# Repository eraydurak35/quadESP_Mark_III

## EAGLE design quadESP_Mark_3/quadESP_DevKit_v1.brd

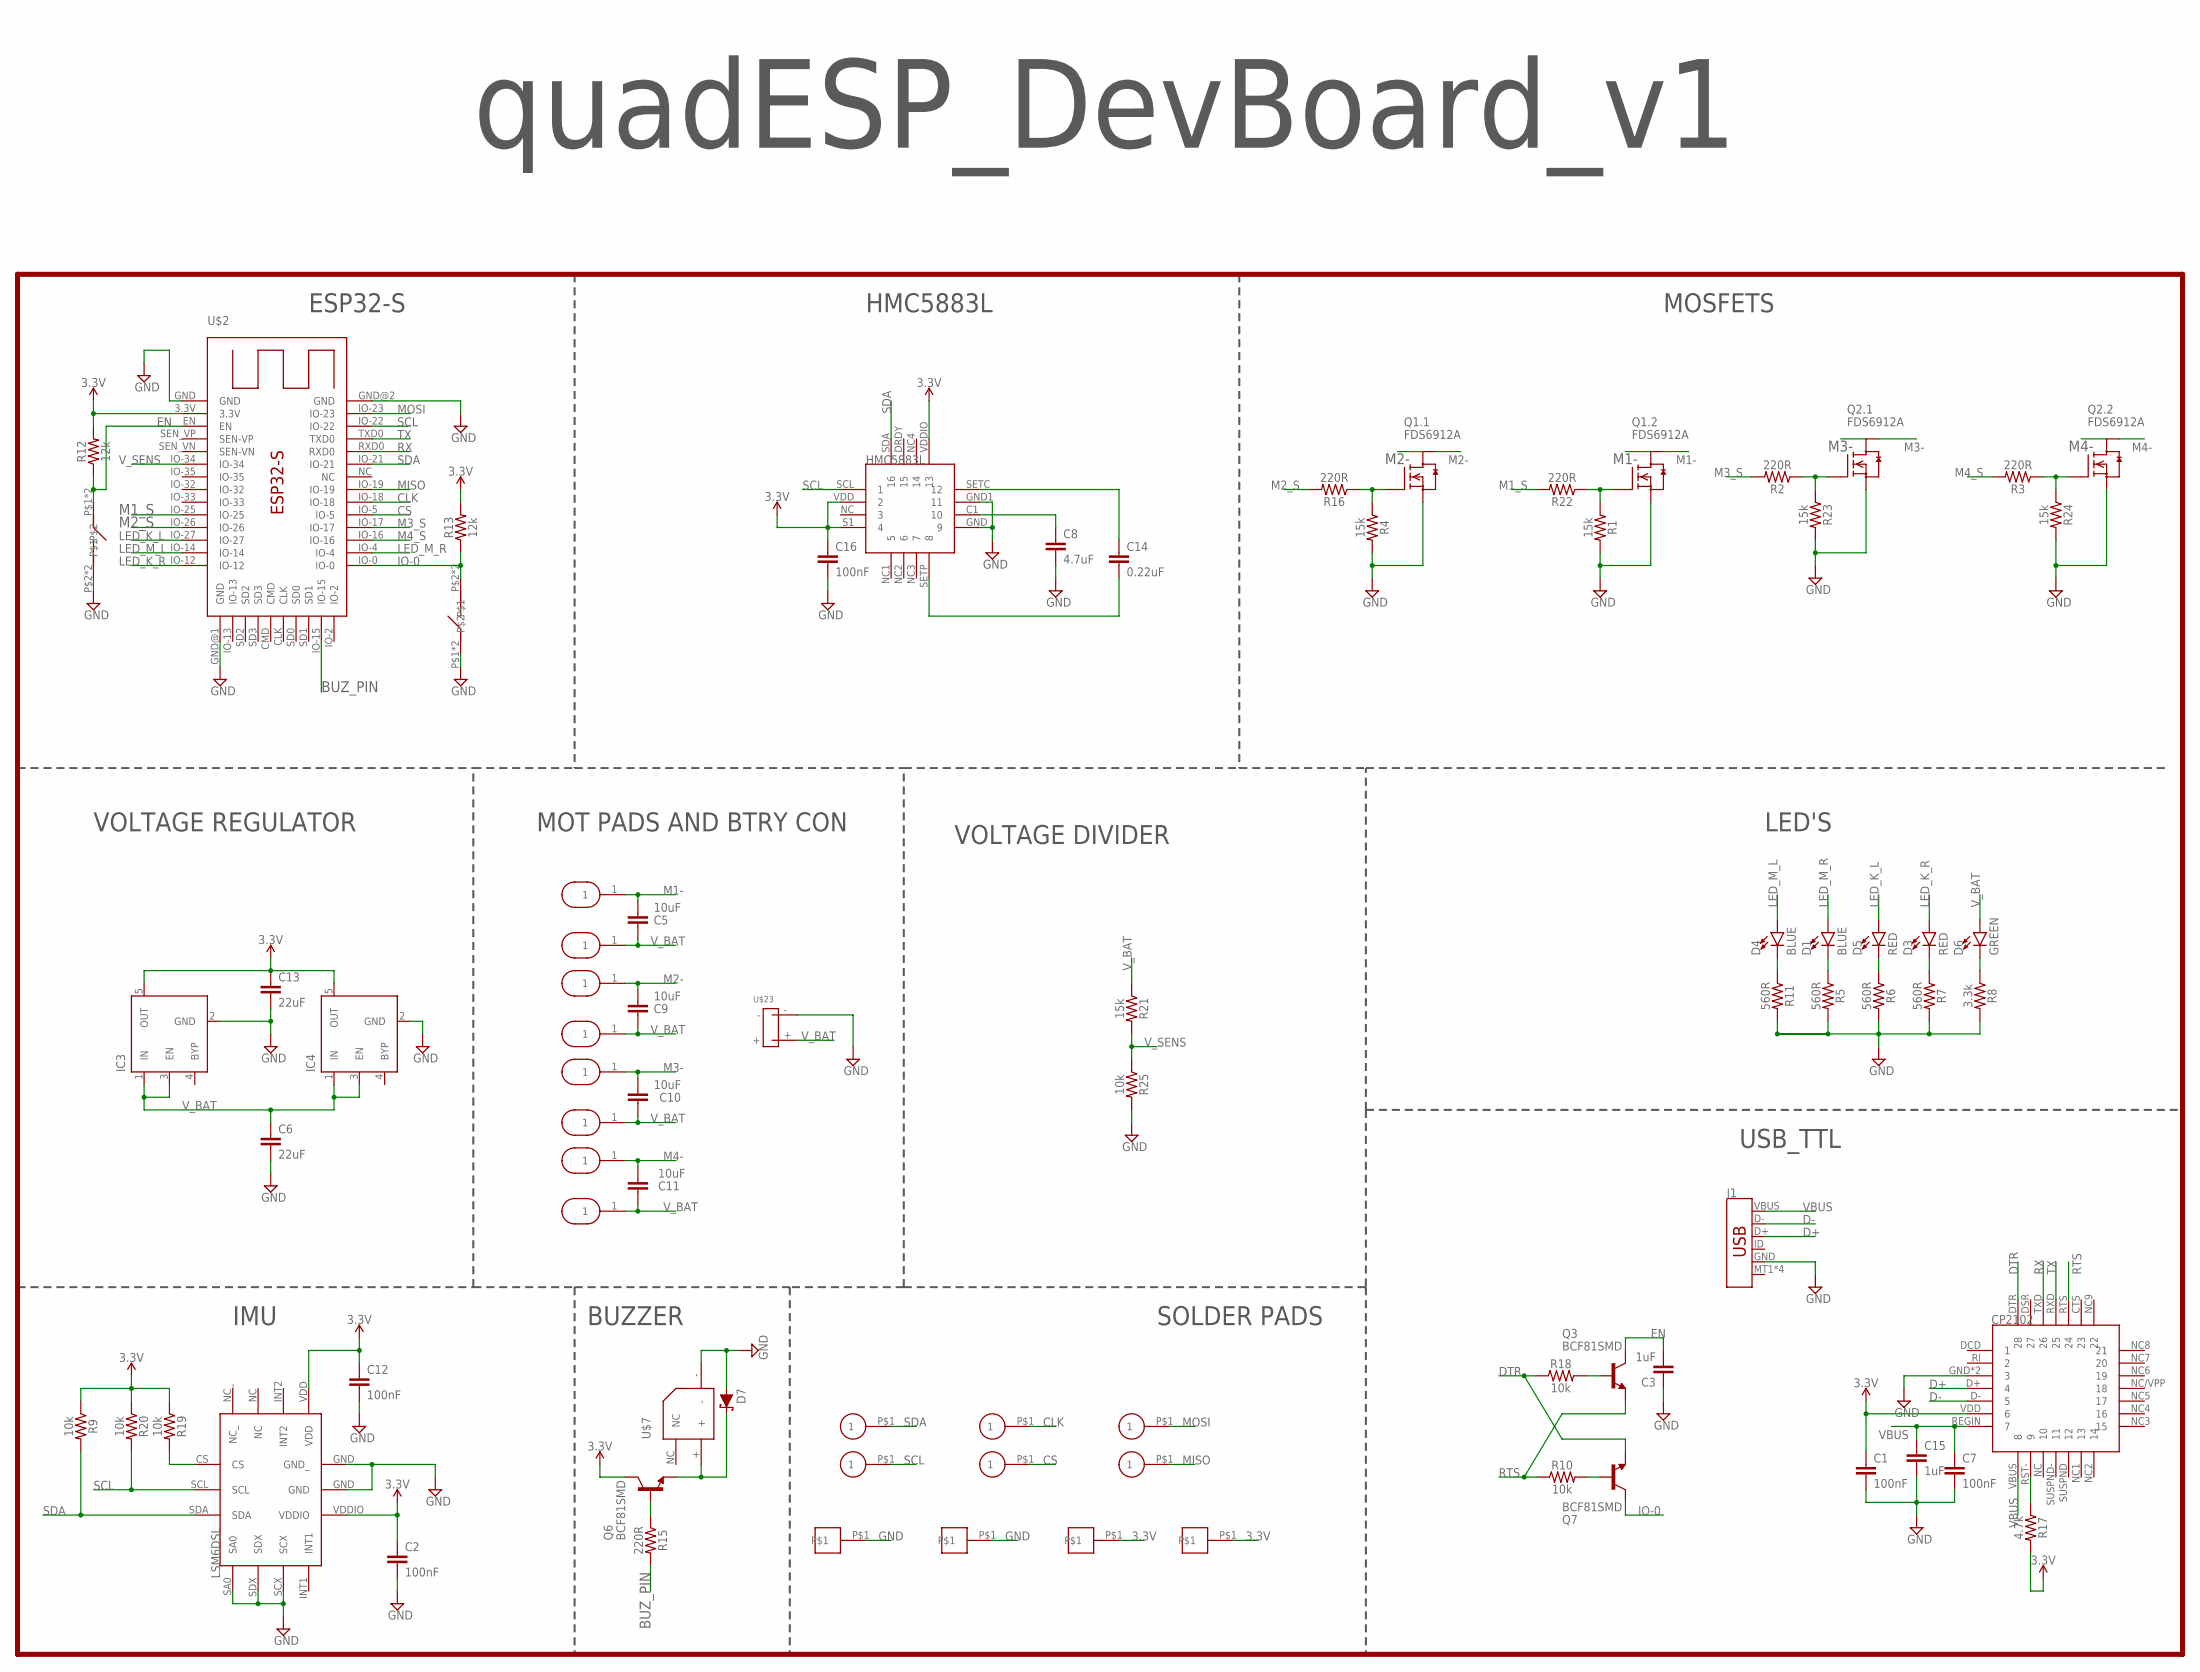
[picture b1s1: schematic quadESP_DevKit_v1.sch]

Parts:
C1, C2, C7, C12, C16: 100nF; 0603
C3, C15: 1uF; 0603
C5, C9, C10, C11: 10uF; 0603
C6, C13: 22uF; 0603
C8: 4.7uF; 0603
C14: 0.22uF; 0603
D1, D4: BLUE; LED-0603
D3, D5: RED; LED-0603
D6: GREEN; LED-0603
D7: 120mA/40V/370mV; SOD-523
IC3, IC4: MIC5219XX; SOT23-5
J1: USB_MICRO-B_SMT; USB-MICROB
Q1, Q2: FDS6912A; SO-8
Q3, Q6, Q7: BCF81SMD; SOT23-BEC
R1, R4, R21, R23, R24: 15k; 0603
R2, R3, R15, R16, R22: 220R; 0603
R5, R6, R7, R11: 560R; 0603
R8: 3.3k; 0603
R9, R10, R18, R19, R20, R25: 10k; 0603
R12, R13: 12k; 0603
R17: 4.7k; 0603
U$1: CP2102_SERIAL_TTL
U$2: ESP32-S
U$3, U$24: TACTILE_SWITCH_4X3X2
U$4, U$15, U$25, U$32, U$33, U$34: SOLDER_PAD_1.2_CIRCLE
U$6: LSM6DSL_6DOF
U$7: PASIVE_BUZZER_5MM_X_5MM_20MM
U$8, U$9, U$10, U$11, U$12, U$13, U$31, U$36: 1.5X2.5_PAD
U$18: HMC5883L
U$19, U$26, U$28, U$30: SOLDER_PAD_1.2_SQUARE
U$23: 2X_SOLDER_PAD

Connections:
3.3V: C1.1, C2.1, C12.1, C13.1, C16.1, IC3.5 (OUT), IC4.5 (OUT), Q6.C, R9.1, R12.2, R13.2, R17.2, R19.1, R20.1, U$1.VDD (6), U$2.3.3V, U$6.VDD, U$6.VDDIO, U$18.S1 (4), U$18.VDD (2), U$18.VDDIO (13), U$28.P$1, U$30.P$1
BUZ_PIN: R15.2, U$2.IO-15
CLK: U$2.IO-18, U$25.P$1
CS: U$2.IO-5, U$32.P$1
D+: J1.D+, U$1.D+ (4)
D-: J1.D-, U$1.D- (5)
DTR: Q7.E, R18.1, U$1.DTR (28)
EN: C3.2, Q3.C, R12.1, U$2.EN, U$3.P$1, U$3.P$4
GND: C1.2, C2.2, C3.1, C6.2, C7.2, C8.2, C12.2, C13.2, C15.2, C16.2, D7.A, IC3.2 (GND), IC4.2 (GND), J1.GND, Q1.1 (S), Q1.3 (S), Q2.1 (S), Q2.3 (S), R1.2, R4.2, R5.2, R6.2, R7.2, R8.2, R11.2, R23.2, R24.2, R25.2, U$1.GND (3), U$1.GND1 (3), U$2.GND, U$2.GND@1 (GND), U$2.GND@2 (GND), U$3.P$2, U$3.P$3, U$6.GND, U$6.GND_, U$6.SA0, U$6.SCX, U$6.SDX, U$7.-, U$18.GND (9), U$18.GND1 (11), U$19.P$1, U$23.-, U$24.P$1, U$24.P$4, U$26.P$1
IO-0: Q7.C, R13.1, U$2.IO-0, U$24.P$2, U$24.P$3
LED_K_L: D5.A, U$2.IO-27
LED_K_R: D3.A, U$2.IO-12
LED_M_L: D4.A, U$2.IO-14
LED_M_R: D1.A, U$2.IO-4
M1-: C5.2, Q1.7 (D), Q1.8 (D), U$31.1
M1_S: R22.2, U$2.IO-25
M2-: C9.2, Q1.5 (D), Q1.6 (D), U$36.1
M2_S: R16.2, U$2.IO-26
M3-: C10.2, Q2.5 (D), Q2.6 (D), U$9.1
M3_S: R2.2, U$2.IO-17
M4-: C11.1, Q2.7 (D), Q2.8 (D), U$11.1
M4_S: R3.2, U$2.IO-16
MISO: U$2.IO-19, U$34.P$1
MOSI: U$2.IO-23, U$33.P$1
unnamed: D1.C, R5.1
unnamed: D5.C, R6.1
unnamed: D3.C, R7.1
unnamed: D6.C, R8.1
unnamed: D4.C, R11.1
unnamed: Q1.4 (G), R4.1, R16.1
unnamed: Q1.2 (G), R1.1, R22.1
unnamed: Q2.4 (G), R2.1, R23.1
unnamed: Q2.2 (G), R3.1, R24.1
unnamed: Q6.B, R15.1
unnamed: R17.1, U$1.RST- (9)
unnamed: D7.C, Q6.E, U$7.+
unnamed: Q3.B, R18.2
unnamed: R19.2, U$6.CS
unnamed: Q7.B, R10.2
unnamed: C14.2, U$18.SETP (8)
unnamed: C8.1, U$18.C1 (10)
unnamed: C14.1, U$18.SETC (12)
RTS: Q3.E, R10.1, U$1.RTS (24)
RX: U$1.TXD (26), U$2.RXD0
SCL: R20.2, U$2.IO-22, U$6.SCL, U$15.P$1, U$18.SCL (1)
SDA: R9.2, U$2.IO-21, U$4.P$1, U$6.SDA, U$18.SDA (16)
TX: U$1.RXD (25), U$2.TXD0
VBUS: C7.1, C15.1, J1.VBUS, U$1.REGIN (7), U$1.VBUS (8)
V_BAT: C5.1, C6.1, C9.1, C10.1, C11.2, D6.A, IC3.1 (IN), IC3.3 (EN), IC4.1 (IN), IC4.3 (EN), R21.1, U$8.1, U$10.1, U$12.1, U$13.1, U$23.+
V_SENS: R21.2, R25.1, U$2.IO-34

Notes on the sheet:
ESP32-S
MOSFETS
LED'S
VOLTAGE DIVIDER
MOT PADS AND BTRY CON
VOLTAGE REGULATOR
IMU
USB_TTL
BUZZER
quadESP_DevBoard_v1
SOLDER PADS
HMC5883L

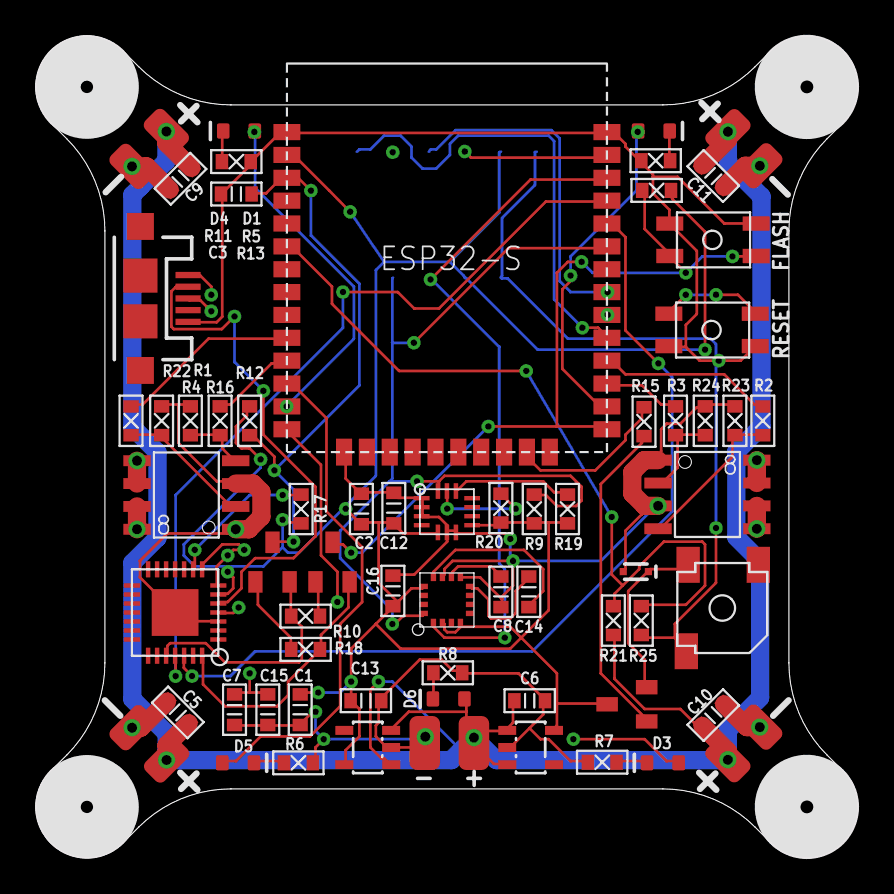
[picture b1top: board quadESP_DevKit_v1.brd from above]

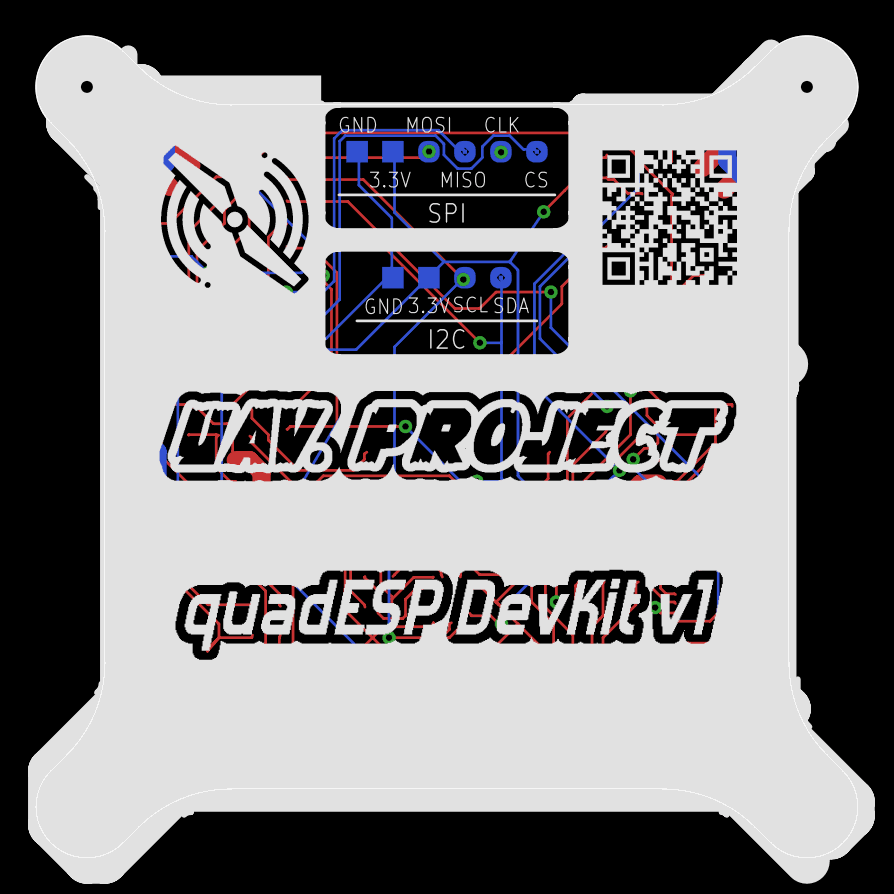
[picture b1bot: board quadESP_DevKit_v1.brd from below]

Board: 4 copper layers, 45.7 x 45.7 mm, 79 parts (10 on the bottom side), 50 nets.

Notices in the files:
parts and their libraries:
m-pad-2.1: License : GNU General Public License version 2 (see bottom)
SparkFun-DiscreteSemi: Licensing: Creative Commons ShareAlike 4.0 International - https://creativecommons.org/licenses/by-sa/4.0
